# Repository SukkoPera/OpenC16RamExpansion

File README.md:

# OpenC16RamExpansion
OpenC16RamExpansion is an Open Hardware 64 Kb RAM Expansion board for the Commodore 16.

## Summary
The board fits the cartridge/expansion port and, in theory, it should instantly give a C16 64 kilobytes of RAM. Unfortunately, the reality is quite different since the C16 was deliberately designed not to be easily expandable, so that the larger RAM would be a selling point of the Plus/4.

This must have been a long-debated feature, since half of the job is done while the other half is missing. In particular, the /RAS, /CAS and MUX signals that are needed to control RAM chips have been brought to the cartridge slot and these cannot actually serve many other purposes. On the other hand, there is no way to disable the internal RAM when an expansion is plugged in the cartridge slot which means that both RAMs will fight for the bus, amounting to a disasterous effect. 

## So What!?
Old expansions used to come with instructions saying how to disable the internal RAM, which was usually obtained by barbarically cutting the power pins altogether. This had the obvious side effect that at that point the machine could ONLY work with the external expansion plugged in, preventing the use of [other cartridges](https://github.com/SukkoPera/OpenC16Cart) (not that many were made, but what about a [SID Card](https://github.com/SukkoPera/ReSeed) or a [User Port Card](https://github.com/SukkoPera/16up)?).

Other boards had output transistors that would somehow "overpower" the outputs of the internal RAM or - worse - force the internal /RAS signal to a high level.

Since both these things are quite likely to damage the - already precarious - internals of your C16, I didn't even think about replicating them. Instead, I have come up with a not-too-hard modification implementing the missing half of the job that Commodore left to be desired. It can be carried out on all C16s in order to let them work with both the internal or external RAM when plugged in. **If you want to use this Expansion, you will have to perform the following modification**:

1. Disconnect pin 1 of U5 and U6 from the mainboard.
2. Connect pin 13 of U12 to pin 1 of U5 and U6.
3. Blob together pins 11 and 12 of U12.
4. Connect pin Z of the expansion slot to that blob with a wire.
5. Solder a 10k resistor between that blob and pin 14 of U12.

This will disable the internal RAM whenever pin Z on the expansion connector is grounded. This is already done on OpenC16RamExpansion but it should be easy to modify any old cart this way.

Now, if you start up your C16 without any expansion plugged in, it should work as usual and report 12277 bytes free. If you start it up with an expansion, you should get 60671. Actually, this is not yet enough to say that the extra RAM is working properly, since you would get the same even without performing any modification. To make sure it is, enter the following BASIC instructions:

POKE 100, 42
PRINT PEEK 16484

If you get **anything else than 42**, then the expansion is working correctly. If you get 42, it is not (that would mean the "second" 16kB of RAM are a replica of the first 16kB).

If you are using a [LittleSixteen V3 board](https://github.com/SukkoPera/LittleSixteen), there is no need to perform any modification, as it is already built-in.

## Releases
If you want to get this board produced, you are recommended to get [the latest release](https://github.com/SukkoPera/OpenC16RamExpansion/releases) rather than the current git version, as the latter might be under development and is not guaranteed to be working.

Every release is accompanied by its Bill Of Materials (BOM) file and any relevant notes about it, which you are recommended to read carefully.

## License
The OpenC16RamExpansion documentation, including the design itself, is copyright &copy; SukkoPera 2019-2021 and is licensed under the [Creative Commons Attribution-NonCommercial-ShareAlike 4.0 International License](https://creativecommons.org/licenses/by-nc-sa/4.0/).

This documentation is distributed *as is* and WITHOUT ANY EXPRESS OR IMPLIED WARRANTIES whatsoever with respect to its functionality, operability or use, including, without limitation, any implied warranties OF MERCHANTABILITY, SATISFACTORY QUALITY, FITNESS FOR A PARTICULAR PURPOSE or infringement. We expressly disclaim any liability whatsoever for any direct, indirect, consequential, incidental or special damages, including, without limitation, lost revenues, lost profits, losses resulting from business interruption or loss of data, regardless of the form of action or legal theory under which the liability may be asserted, even if advised of the possibility or likelihood of such damages.

## Support the Project
If you want to get some boards manufactured, you can get them from PCBWay through this link:

You get my gratitude and cheap, professionally-made and good quality PCBs, I get some credit that will help with this and [other projects](https://www.pcbway.com/project/member/shareproject/?bmbid=41100). You won't even have to worry about the various PCB options, it's all pre-configured for you!

Also, if you still have to register, [you can use this link](https://www.pcbway.com/setinvite.aspx?inviteid=41100) to get some bonus initial credit (and yield me some more).

You can also buy me a coffee if you want:

## Credits
This board was laid out only by looking at [various C16/Plus/4 schematics](http://www.zimmers.net/anonftp/pub/cbm/schematics/computers/plus4/index.html) and pictures (mostly low-resolution) of [similar expansions from back in the day](http://plus4world.powweb.com/hardware) I found on the Net, I have never seen one in real life:
* [Rex Speichererweiterung](https://plus4world.powweb.com/hardware/Rex_Speichererweiterung)
* [Jurek's 64K Memory Expansion](https://plus4world.powweb.com/hardware/Jureks_64K_Memory_Expansion)
* [Dela 32K](https://plus4world.powweb.com/hardware/Dela_32K)

So thanks to the makers of those expansions and to Zimmers and Plus/4 World for cataloguing them.

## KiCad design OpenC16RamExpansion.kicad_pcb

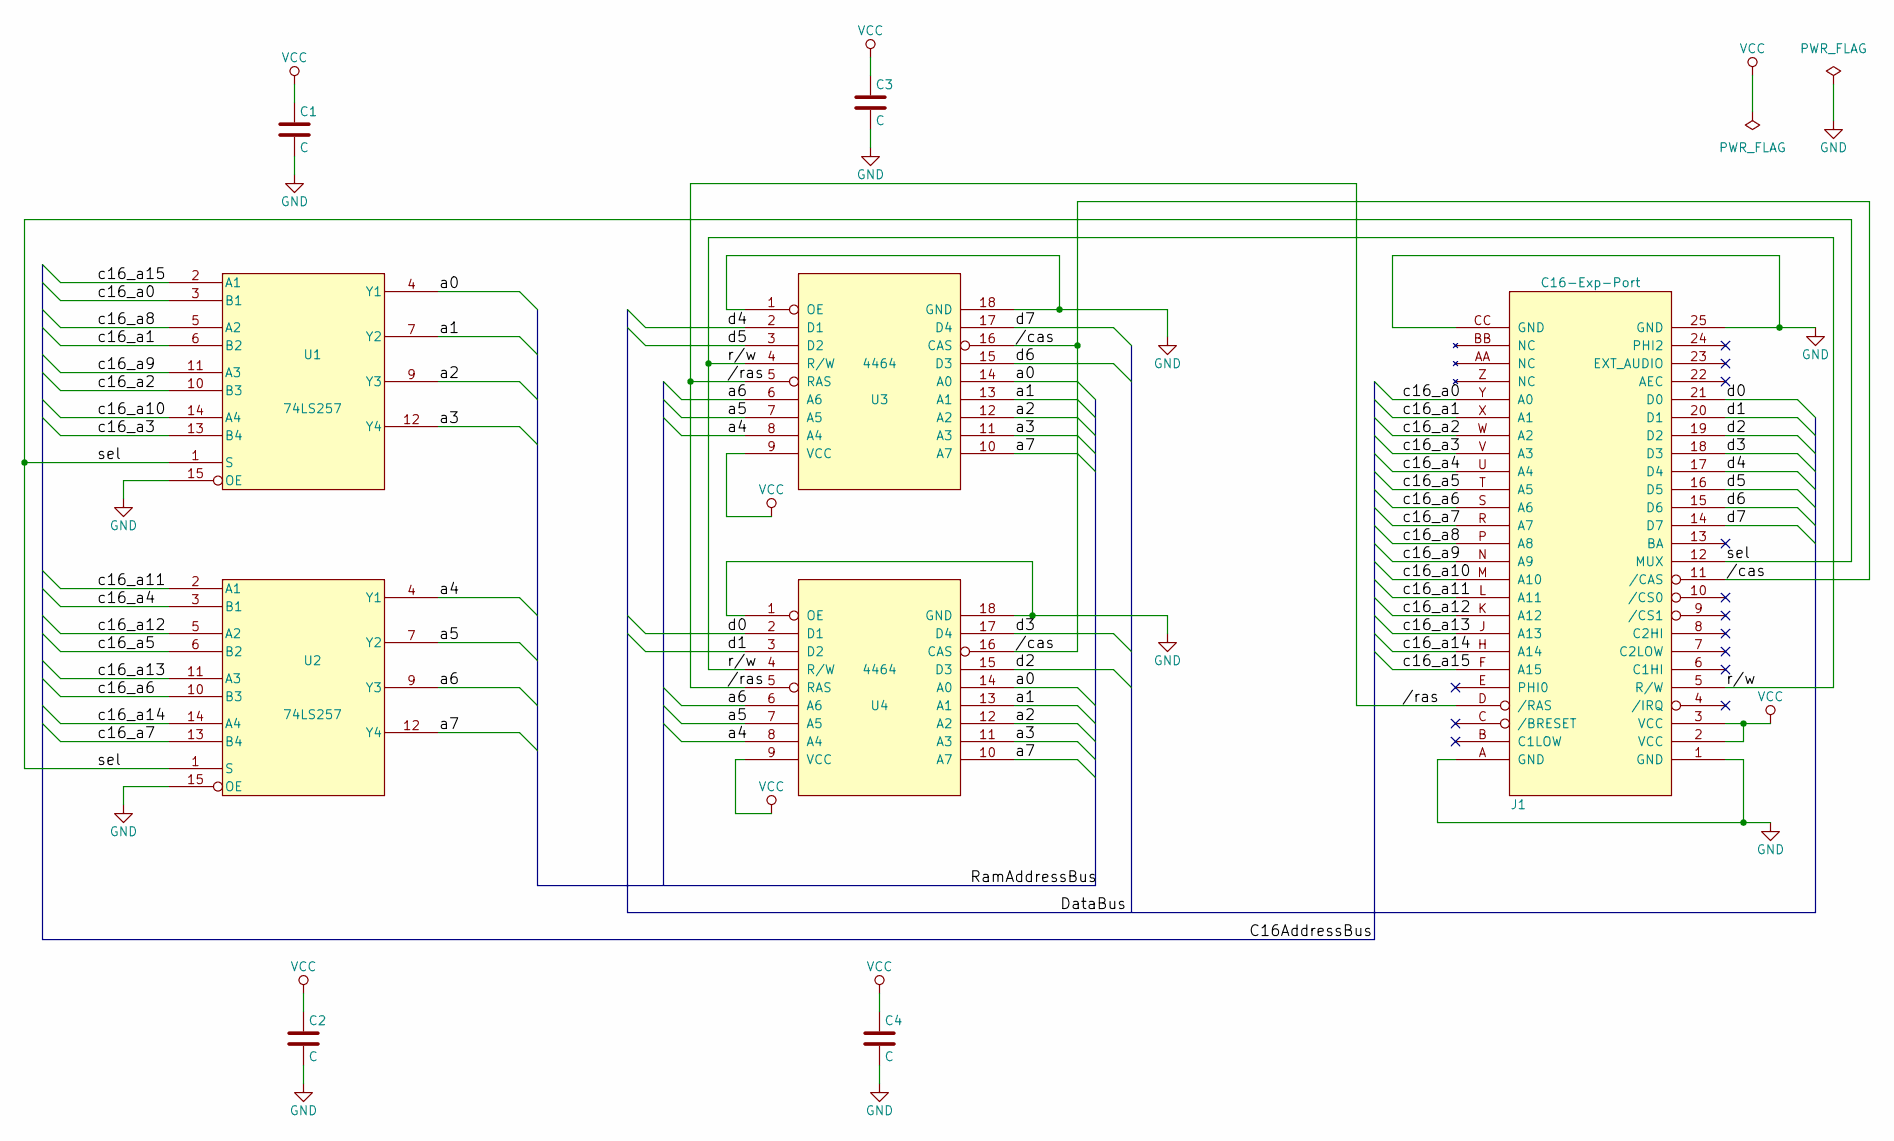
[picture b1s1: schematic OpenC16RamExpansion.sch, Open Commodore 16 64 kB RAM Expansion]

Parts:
C1, C2, C3, C4: C; C_0805_HandSoldering
J1: C16-Exp-Port; C16_Cart_Conn
U1, U2: 74LS257; DIP-16_W7.62mm_Socket
U3, U4: 4464; DIP-18_W7.62mm_Socket

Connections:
//cas: J1.11 (/CAS), U3.16 (CAS), U4.16 (CAS)
//ras: J1.D (/RAS), U3.5 (RAS), U4.5 (RAS)
/a0: U1.4 (Y1), U3.14 (A0), U4.14 (A0)
/a1: U1.7 (Y2), U3.13 (A1), U4.13 (A1)
/a2: U1.9 (Y3), U3.12 (A2), U4.12 (A2)
/a3: U1.12 (Y4), U3.11 (A3), U4.11 (A3)
/a4: U2.4 (Y1), U3.8 (A4), U4.8 (A4)
/a5: U2.7 (Y2), U3.7 (A5), U4.7 (A5)
/a6: U2.9 (Y3), U3.6 (A6), U4.6 (A6)
/a7: U2.12 (Y4), U3.10 (A7), U4.10 (A7)
/c16_a0: J1.Y (A0), U1.3 (B1)
/c16_a1: J1.X (A1), U1.6 (B2)
/c16_a2: J1.W (A2), U1.10 (B3)
/c16_a3: J1.V (A3), U1.13 (B4)
/c16_a4: J1.U (A4), U2.3 (B1)
/c16_a5: J1.T (A5), U2.6 (B2)
/c16_a6: J1.S (A6), U2.10 (B3)
/c16_a7: J1.R (A7), U2.13 (B4)
/c16_a8: J1.P (A8), U1.5 (A2)
/c16_a9: J1.N (A9), U1.11 (A3)
/c16_a10: J1.M (A10), U1.14 (A4)
/c16_a11: J1.L (A11), U2.2 (A1)
/c16_a12: J1.K (A12), U2.5 (A2)
/c16_a13: J1.J (A13), U2.11 (A3)
/c16_a14: J1.H (A14), U2.14 (A4)
/c16_a15: J1.F (A15), U1.2 (A1)
/d0: J1.21 (D0), U4.2 (D1)
/d1: J1.20 (D1), U4.3 (D2)
/d2: J1.19 (D2), U4.15 (D3)
/d3: J1.18 (D3), U4.17 (D4)
/d4: J1.17 (D4), U3.2 (D1)
/d5: J1.16 (D5), U3.3 (D2)
/d6: J1.15 (D6), U3.15 (D3)
/d7: J1.14 (D7), U3.17 (D4)
/r/w: J1.5 (R/W), U3.4 (R/W), U4.4 (R/W)
/sel: J1.12 (MUX), U1.1 (S), U2.1 (S)
GND: C1.2, C2.2, C3.2, C4.2, J1.1 (GND), J1.25 (GND), J1.A (GND), J1.CC (GND), U1.8 (GND), U1.15 (OE), U2.8 (GND), U2.15 (OE), U3.1 (OE), U3.18 (GND), U4.1 (OE), U4.18 (GND)
VCC: C1.1, C2.1, C3.1, C4.1, J1.2 (VCC), J1.3 (VCC), U1.16 (VCC), U2.16 (VCC), U3.9 (VCC), U4.9 (VCC)

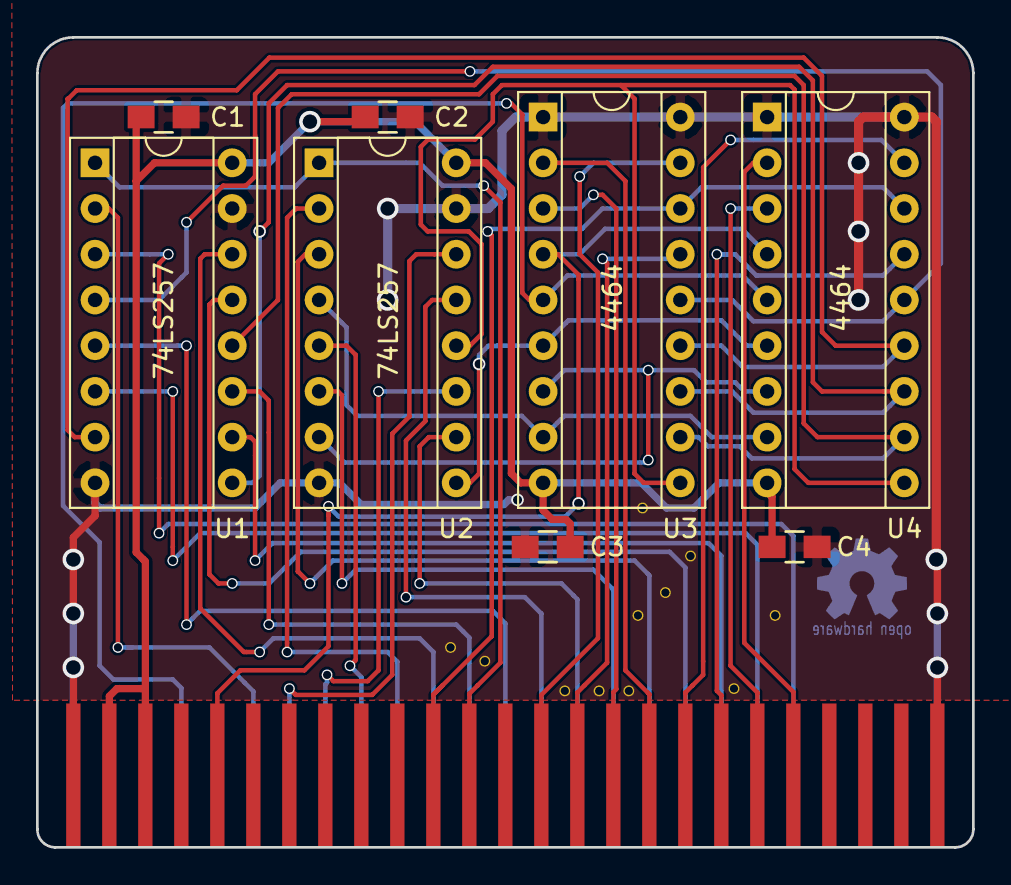
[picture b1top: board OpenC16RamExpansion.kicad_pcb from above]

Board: 2 copper layers, 52.0 x 45.0 mm, 9 parts (0 on the bottom side), 38 nets.

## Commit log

2017-08-20 Initial commit - WORK IN PROGRESS!
2017-08-20 Add Expansion Port symbol and footprint
2017-08-21 Complete schematics
2017-08-21 Working on PCB
2017-08-21 Add .gitignore
2017-08-23 Almost there...
2017-08-23 V1.0!
2017-08-23 Make connector footprint larger and taller
2017-08-23 Switch to new connector and improve back ground plane
2017-09-02 Make connector lower again and smooth orners
2017-09-02 Add decoupling caps
2017-09-29 Make board 0.5mm wider and space edge contacts 2.00 apart
2017-09-29 Smooth top corners Radius is 2mm. Bottom is 1.5mm
2017-09-29 Zero pad clearance
2017-09-29 Reduce antipad clearance
2017-09-29 Bump version
2017-09-29 Fix 3D models
2018-01-01 Space edge connector pins 2.0mm apart, improve ground plane and some other tweaks
2018-01-01 Make board slightly larger
2018-01-07 Final touches for V2
2018-01-07 Add README
2018-01-07 Edit README
2018-01-07 Add inspirational images
2022-10-30 Finalize README
2026-02-13 Change coffee donation image link in README
    Updated the coffee donation link image in the README.
